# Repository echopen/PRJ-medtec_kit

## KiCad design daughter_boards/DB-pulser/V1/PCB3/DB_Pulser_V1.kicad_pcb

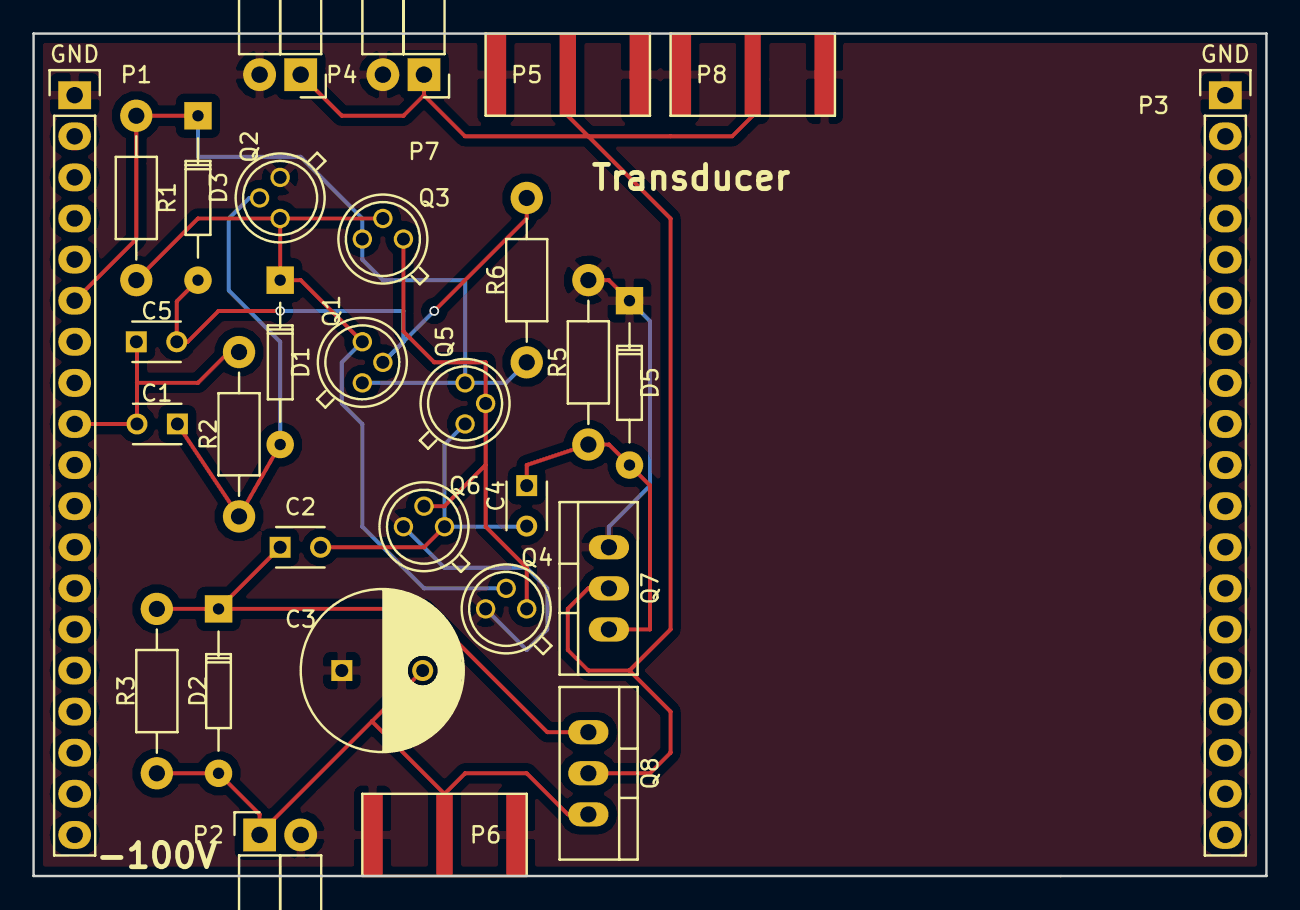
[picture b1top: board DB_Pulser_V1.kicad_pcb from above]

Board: 2 copper layers, 76.2 x 52.1 mm, 30 parts (0 on the bottom side), 12 nets.

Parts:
C1: 100p; C_Disc_D3_P2.5
C2, C4: 100n; C_Disc_D3_P2.5
C3: 33u; C_Radial_D10_L13_P5
C5: 220p; C_Disc_D3_P2.5
D1: BAT48 0.6V; Diode_DO-35_SOD27_Horizontal_RM10
D2, D5: BZD23-18; Diode_DO-35_SOD27_Horizontal_RM10
D3: D1N4148; Diode_DO-35_SOD27_Horizontal_RM10
P1, P3: CONN_01X19; Header_1x19
P2, P4, P7: CONN_01X02; Socket_Strip_Angled_1x02
P5, P6, P8: SMA
Q1, Q4, Q6: 2N2907; TO-18_3Pin
Q2, Q3, Q5: 2N2222; TO-18_3Pin
Q7: IRF9610; TO-220_Neutral123_Vertical
Q8: IRF610; TO-220_Neutral123_Vertical
R1: 1k; Resistor_Horizontal_RM10mm
R2: 22; Resistor_Horizontal_RM10mm
R3, R5: 1M; Resistor_Horizontal_RM10mm
R6: 100k; Resistor_Horizontal_RM10mm

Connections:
GND: C3.1, D5.1, P1.1, P2.2, P3.1, P4.2, P5.2, P6.2, P7.2, P8.2, Q2.1, Q4.3, Q6.3, Q7.3, R5.1
unnamed: C1.1, D1.2, Q2.2, R2.1
unnamed: C1.2, C5.1, P1.9, R2.2
unnamed: C2.1, D2.1, Q8.1, R3.1
unnamed: C2.2, C4.2, Q5.1, Q6.1
unnamed: C3.2, D2.2, P2.1, P6.1, Q8.3, R3.2
unnamed: C4.1, D5.2, Q7.1, R5.2
unnamed: C5.2, D3.2, Q1.2, R6.1
unnamed: D1.1, Q1.3, Q2.3, Q3.2, Q4.2, R1.2
unnamed: D3.1, P1.6, Q1.1, Q3.3, Q5.3, R1.1, R6.2
unnamed: P4.1, P5.1, P7.1, P8.1, Q7.2, Q8.2
unnamed: Q3.1, Q4.1, Q5.2, Q6.2

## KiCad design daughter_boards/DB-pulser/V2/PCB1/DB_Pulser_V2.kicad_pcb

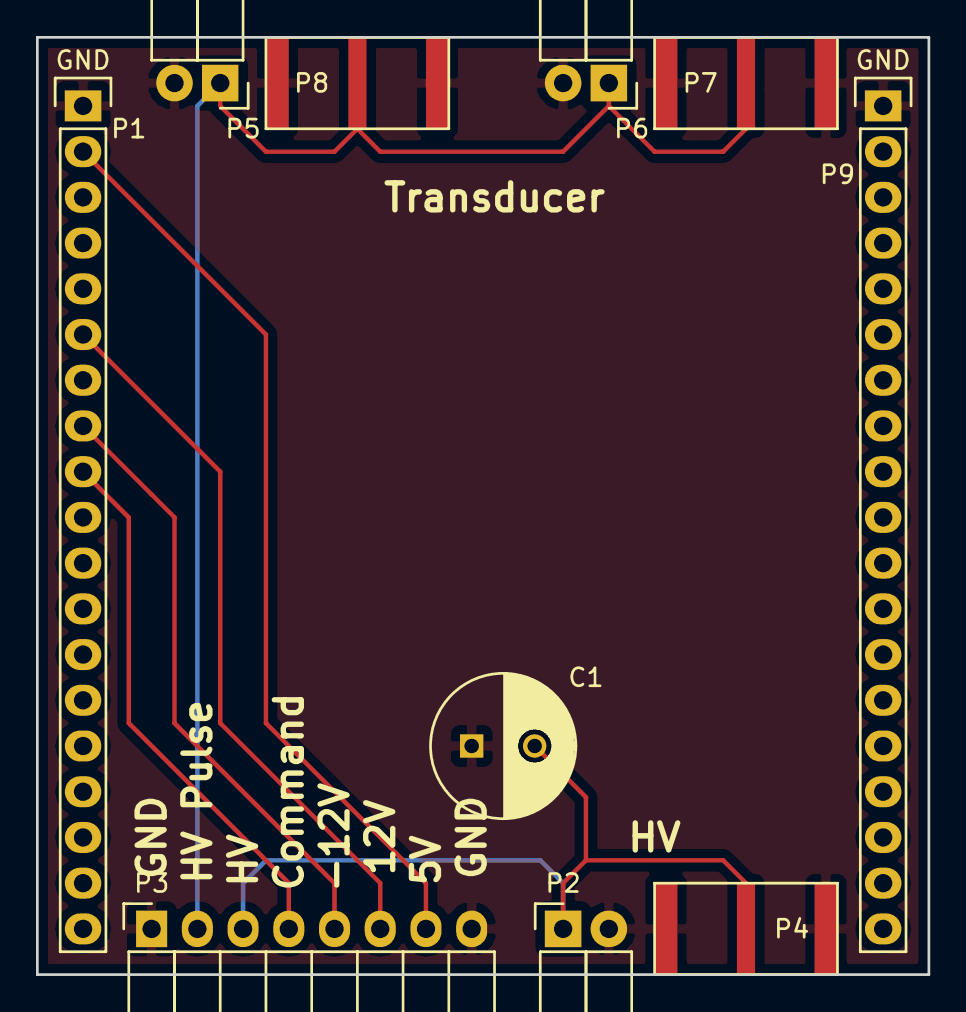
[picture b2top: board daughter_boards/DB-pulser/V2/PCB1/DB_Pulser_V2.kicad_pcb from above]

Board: 2 copper layers, 49.5 x 52.1 mm, 10 parts (0 on the bottom side), 7 nets.

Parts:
C1: 33u (150V); CP_TH_common
P1, P9: CONN_01X19; Header_pin_1x19
P2, P5, P6: CONN_01X02; Socket_Strip_Angled_1x02
P3: CONN_01X08; Socket_Strip_Angled_1x08
P4, P7, P8: SMA

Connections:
GND: C1.1, P1.1, P2.2, P3.1, P3.8, P4.2, P5.2, P6.2, P7.2, P8.2, P9.1
unnamed: C1.2, P2.1, P3.6, P4.1
unnamed: P1.2, P3.2
unnamed: P1.6, P3.3
unnamed: P1.8, P3.4
unnamed: P1.9, P3.5
unnamed: P3.7, P5.1, P6.1, P7.1, P8.1

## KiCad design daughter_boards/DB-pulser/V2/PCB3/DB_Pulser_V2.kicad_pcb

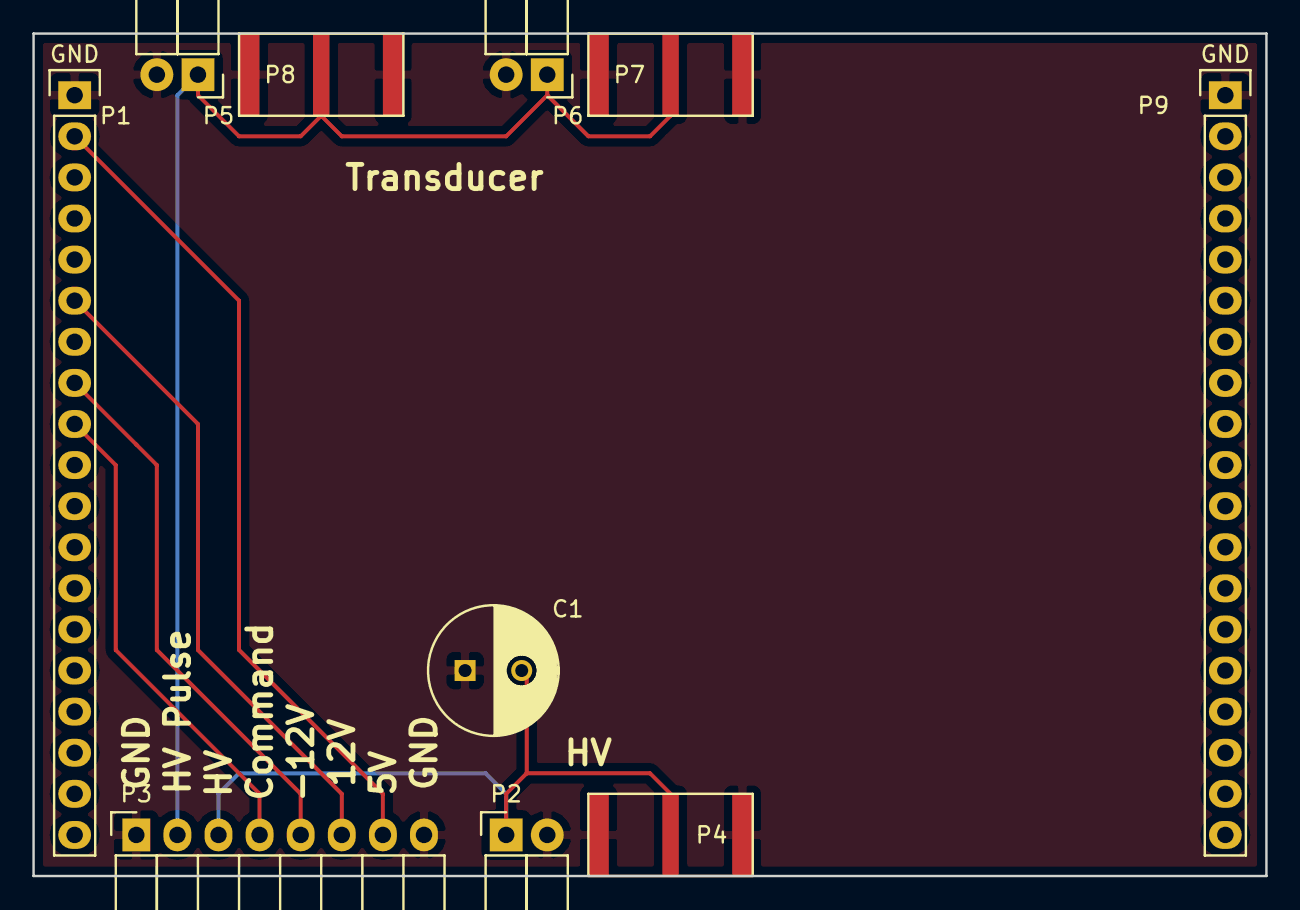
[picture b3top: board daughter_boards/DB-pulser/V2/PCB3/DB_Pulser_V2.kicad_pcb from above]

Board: 2 copper layers, 76.2 x 52.1 mm, 10 parts (0 on the bottom side), 7 nets.

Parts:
C1: 33u (150V); CP_TH_common
P1, P9: CONN_01X19; Header_1x19
P2, P5, P6: CONN_01X02; Socket_Strip_Angled_1x02
P3: CONN_01X08; Socket_Strip_Angled_1x08
P4, P7, P8: SMA

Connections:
GND: C1.1, P1.1, P2.2, P3.1, P3.8, P4.2, P5.2, P6.2, P7.2, P8.2, P9.1
unnamed: C1.2, P2.1, P3.3, P4.1
unnamed: P1.2, P3.7
unnamed: P1.6, P3.6
unnamed: P1.8, P3.5
unnamed: P1.9, P3.4
unnamed: P3.2, P5.1, P6.1, P7.1, P8.1

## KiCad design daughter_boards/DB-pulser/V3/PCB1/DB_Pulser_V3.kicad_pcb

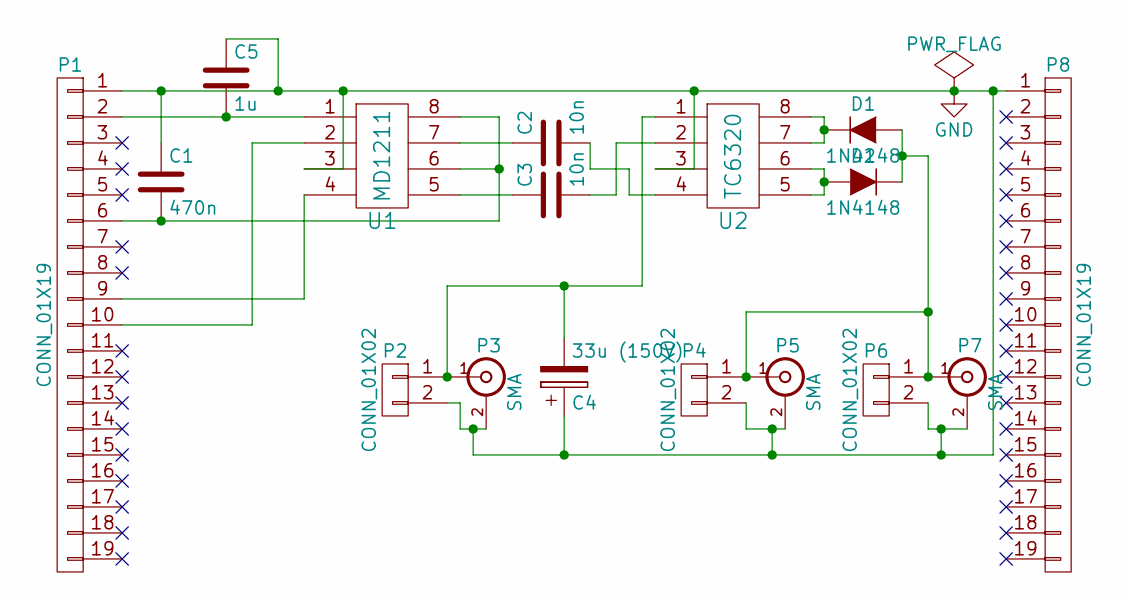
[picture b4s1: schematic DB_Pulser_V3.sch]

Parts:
C1: 470n; C_TH_common
C2, C3: 10n; C_TH_common
C4: 33u (150V); CP_TH_common
C5: 1u; C_TH_common
D1, D2: 1N4148; D_TH_common
P1, P8: CONN_01X19; Header_pin_1x19
P2, P4, P6: CONN_01X02; Socket_Strip_Angled_1x02
P3, P5, P7: SMA
U1: MD1211; SOIJ-8_5.3x5.3mm_Pitch1.27mm
U2: TC6320; SOIJ-8_5.3x5.3mm_Pitch1.27mm

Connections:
GND: C1.1, C4.1, C5.1, P1.1, P2.2, P3.2 (Ext), P4.2, P5.2 (Ext), P6.2, P7.2 (Ext), P8.1, U1.3, U2.3
unnamed: C1.2, P1.6, U1.6, U1.8
unnamed: C2.1, U1.7
unnamed: C2.2, U2.4
unnamed: C3.1, U1.5
unnamed: C3.2, U2.2
unnamed: C4.2, P2.1, P3.1 (In), U2.1
unnamed: C5.2, P1.2, U1.1
unnamed: D1.1 (K), U2.7, U2.8
unnamed: D1.2 (A), D2.1 (K), P4.1, P5.1 (In), P6.1, P7.1 (In)
unnamed: D2.2 (A), U2.5, U2.6
unnamed: P1.9, U1.4
unnamed: P1.10, U1.2

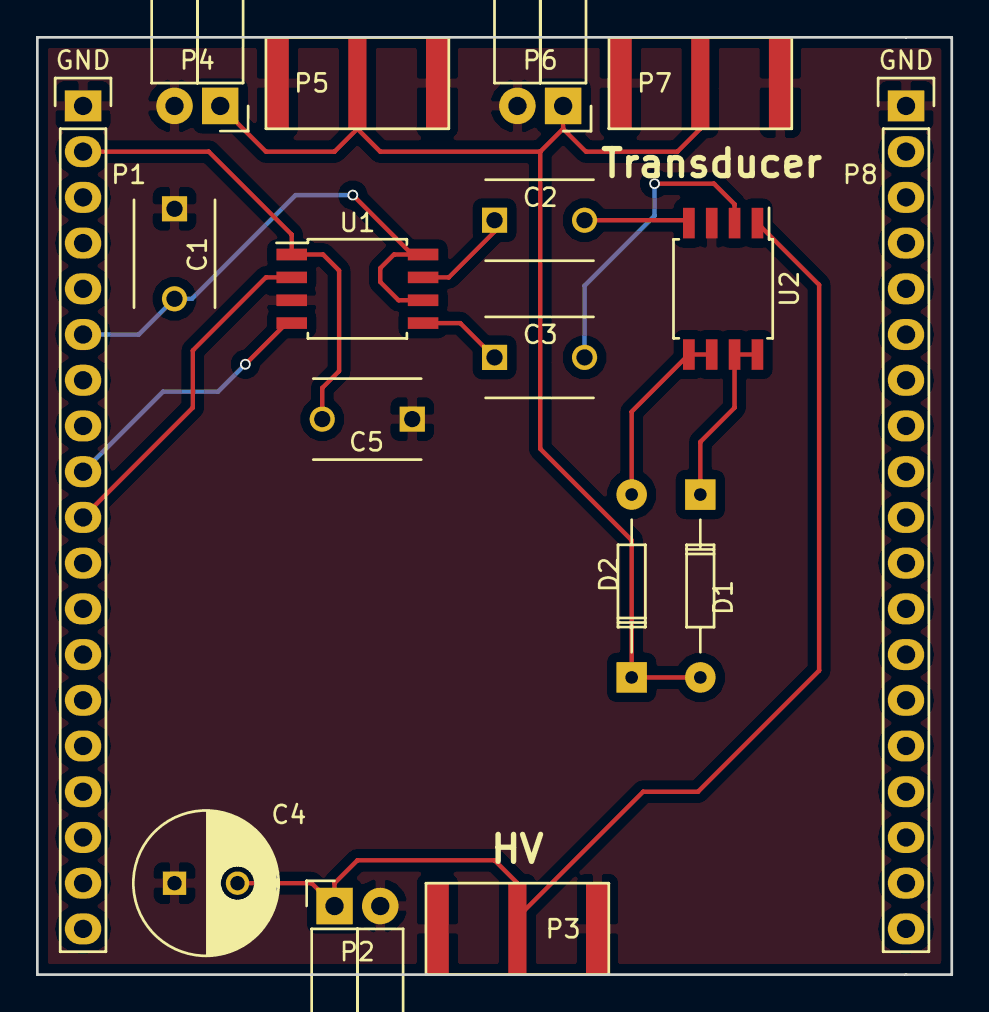
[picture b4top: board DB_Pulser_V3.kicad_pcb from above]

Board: 2 copper layers, 50.8 x 52.1 mm, 17 parts (0 on the bottom side), 13 nets.

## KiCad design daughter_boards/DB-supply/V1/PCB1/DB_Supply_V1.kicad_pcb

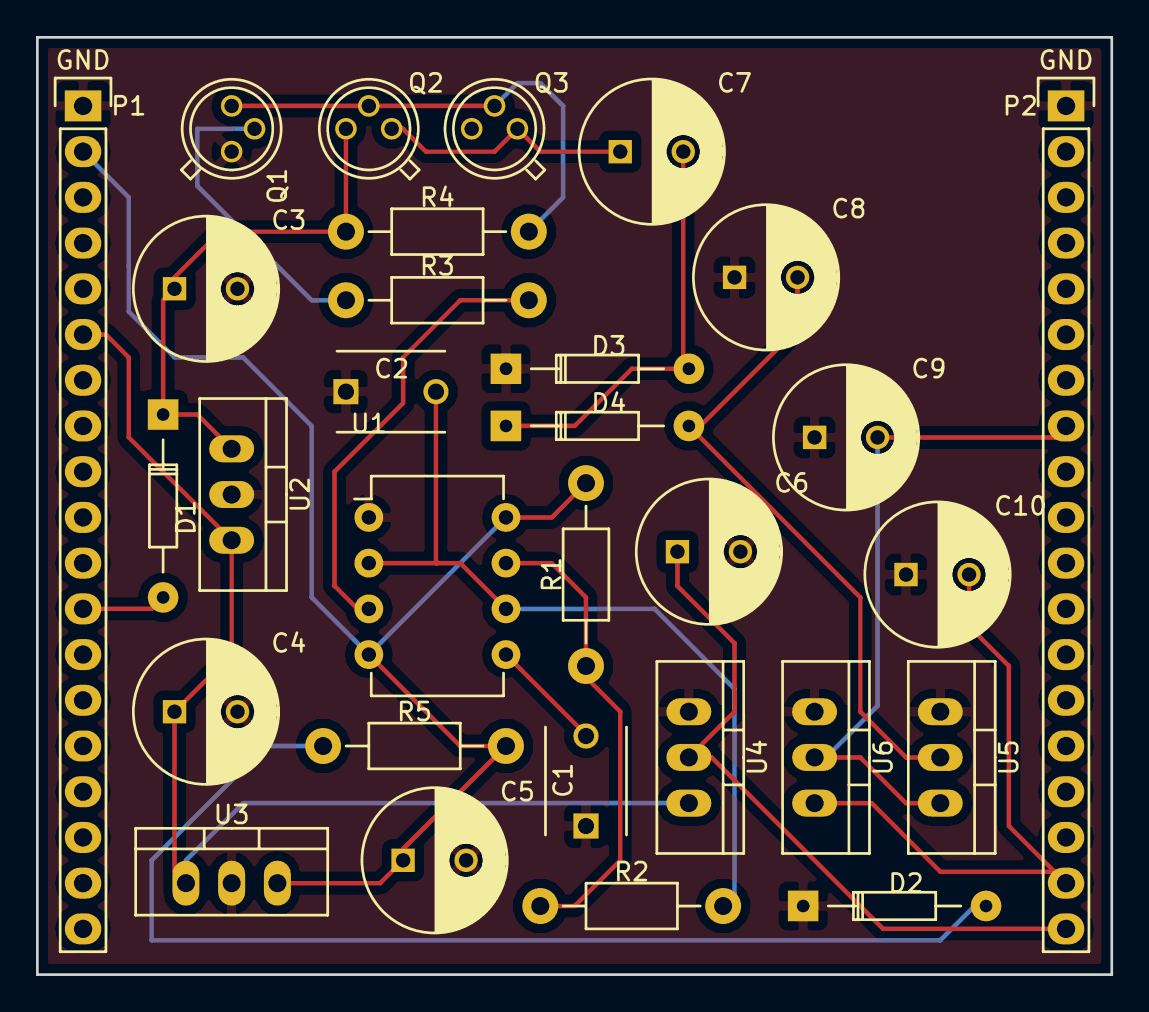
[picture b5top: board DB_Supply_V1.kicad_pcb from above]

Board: 2 copper layers, 59.7 x 52.1 mm, 30 parts (0 on the bottom side), 18 nets.

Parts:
C1: 10n; C_TH_common
C2: 47n; C_TH_common
C3: 220u; CP_TH_common
C4, C5, C6, C7, C8, C9, C10: 47u; CP_TH_common
D1, D3, D4: 1N4001; D_TH_common
D2: LED; D_TH_common
P1, P2: CONN_01X19; Header_pin_1x19
Q1, Q2: 2N2222; TO-18_TH_common
Q3: 2N2907; TO-18_TH_common
R1: 2.2k; Resistor_TH_common
R2: 12k; Resistor_TH_common
R3: 3.3k; Resistor_TH_common
R4: 1.8k; Resistor_TH_common
R5: 270; Resistor_TH_common
U1: LM555N; DIP-8_W7.62mm
U2: LM2940T-12.0/NOPB; TO-220_TH_common
U3: LM2940T-5.0/NOPB; TO-220_TH_common
U4: LM1117T-3.3/NOPB; TO-220_TH_common
U5: LM2990T-12.0/NOPB; TO-220_TH_common
U6: LM2990T-5.0/NOPB; TO-220_TH_common

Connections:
GND: C1.1, C2.1, C3.2, C4.2, C5.2, C6.2, C8.1, C9.1, C10.1, D2.1, D3.1, P1.1, P2.1, Q1.1, Q3.3, U1.1, U2.2, U3.2, U4.1, U5.1, U6.1
unnamed: C1.2, U1.5
unnamed: C2.2, R2.2, U1.2, U1.6
unnamed: C3.1, D1.1, Q2.3, R4.1, U2.1
unnamed: C4.1, P1.6, U2.3, U3.1, U4.3
unnamed: C6.1, P2.19, U4.2
unnamed: C7.1, Q2.1, Q3.1
unnamed: C7.2, D3.2, D4.1
unnamed: C8.2, D4.2, U5.2
unnamed: C9.2, P2.8, U5.3, U6.2
unnamed: C10.2, P2.18, U6.3
unnamed: D1.2, P1.12
unnamed: D2.2, R5.1
unnamed: Q1.2, R3.1
unnamed: Q1.3, Q2.2, Q3.2, R4.2
unnamed: R1.1, R2.1, U1.7
unnamed: R3.2, U1.3
VCC: C5.1, P1.2, R1.2, R5.2, U1.4, U1.8, U3.3

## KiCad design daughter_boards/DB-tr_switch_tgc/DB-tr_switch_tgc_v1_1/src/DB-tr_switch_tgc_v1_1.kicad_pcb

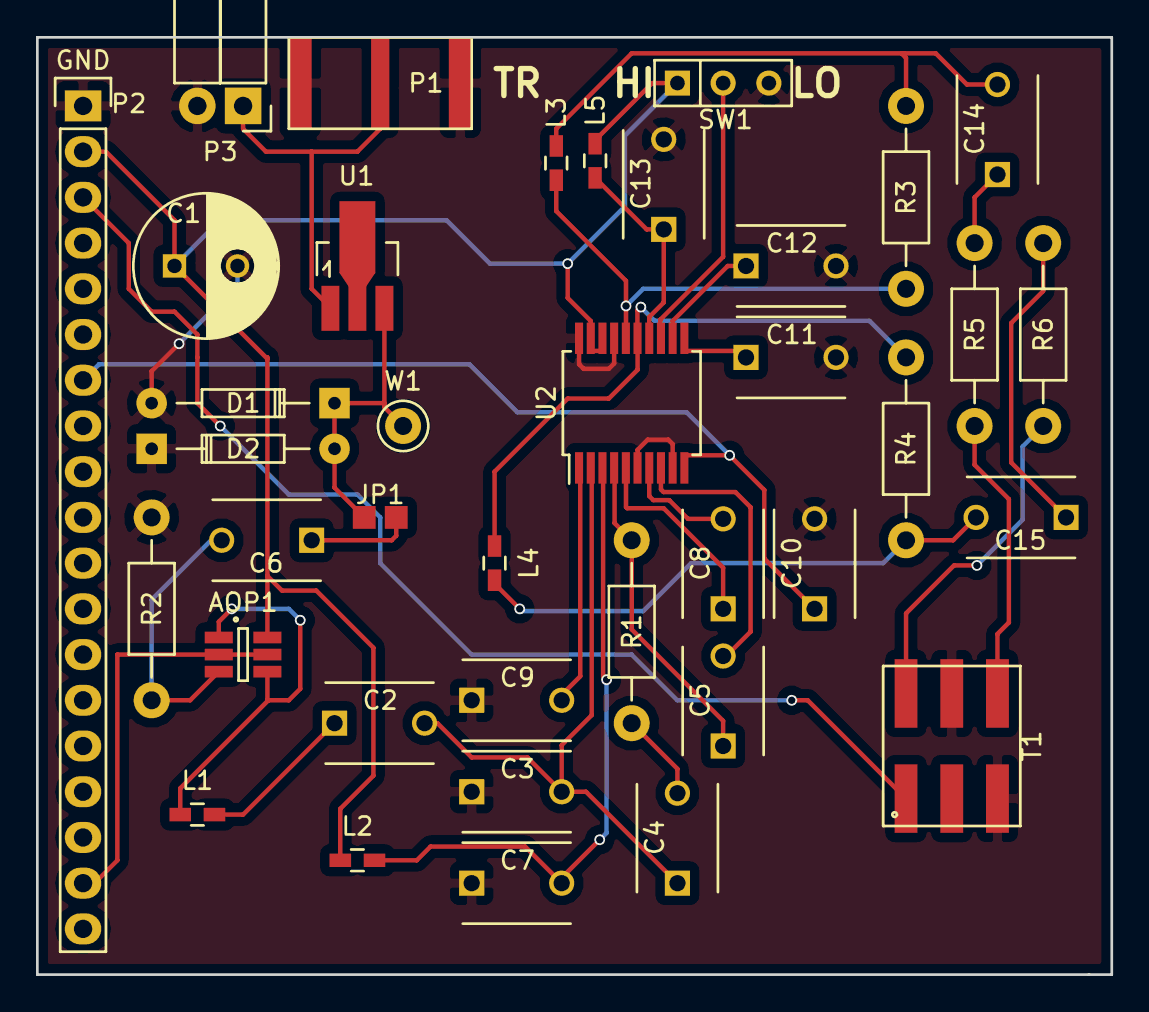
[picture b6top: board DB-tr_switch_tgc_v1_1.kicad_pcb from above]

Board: 2 copper layers, 59.7 x 52.1 mm, 38 parts (0 on the bottom side), 31 nets.

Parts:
AOP1: OPA625; SOT-23-6_Handsoldering(OPA625)
C1: 10u; CP_TH_common
C2, C5, C7, C8, C9, C11, C12, C13, C14, C15: 100n; C_TH_common
C3: 22p; C_TH_common
C4: 18n; C_TH_common
C6, C10: 1n; C_TH_common
D1, D2: 1N4148; D_TH_common
JP1: JUMPER; Jumper
L1, L2, L3, L4, L5: 120n; CMS_0603
P1: SMA
P2: CONN_01X19; Header_pin_angled_1x19
P3: CONN_01X02; Socket_Strip_Angled_1x02
R1: 274; Resistor_TH_common
R2: 220; Resistor_TH_common
R3, R4: 100; Resistor_TH_common
R5, R6: 237; Resistor_TH_common
SW1: SWITCH_INV; SW_Micro_SPST
T1: TRANSFO_6pins; Transfo_6pins(coilcraft)
U1: MD0100; SOT89-3_Housing_Handsoldering
U2: AD8331; SSOP-20_5.3x7.2mm_Pitch0.65mm
W1: TEST_1P; Test_Point_Keystone_5000-5004_Miniature

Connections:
GND: C1.2, C3.1, C7.1, C9.1, C10.2, C11.2, C12.2, C13.2, D1.2, D2.1, P1.2, P2.1, P3.2, R2.2, SW1.3, T1.2, T1.4, U2.6, U2.9, U2.17, U2.20
unnamed: AOP1.1, AOP1.4, L1.1
unnamed: AOP1.2, AOP1.5, P2.18
unnamed: AOP1.3, C6.2, R2.1
unnamed: AOP1.6, C1.1, L2.1, L5.2, P2.2, SW1.1, U2.18, U2.19
unnamed: C2.1, L1.2
unnamed: C2.2, C3.2, C4.1, U2.2
unnamed: C4.2, R1.1
unnamed: C5.1, R1.2, U2.4
unnamed: C5.2, U2.8
unnamed: C6.1, JP1.2
unnamed: C7.2, L2.2, U2.3
unnamed: C8.1, U2.5
unnamed: C8.2, U2.7
unnamed: C9.2, U2.1
unnamed: C10.1, P2.7, U2.10
unnamed: C11.1, U2.11
unnamed: C12.1, U2.12
unnamed: C13.1, L5.1, U2.14
unnamed: C14.1, R5.2
unnamed: C14.2, L3.2, R3.1
unnamed: C15.1, R6.2
unnamed: C15.2, L4.2, R4.1
unnamed: D1.1, D2.2, JP1.1, U1.3, W1.1
unnamed: L3.1, R3.2, U2.16
unnamed: L4.1, R4.2, U2.15
unnamed: P1.1, P3.1, U1.1
unnamed: P2.3, T1.6
unnamed: R5.1, T1.3
unnamed: R6.1, T1.1
unnamed: SW1.2, U2.13
